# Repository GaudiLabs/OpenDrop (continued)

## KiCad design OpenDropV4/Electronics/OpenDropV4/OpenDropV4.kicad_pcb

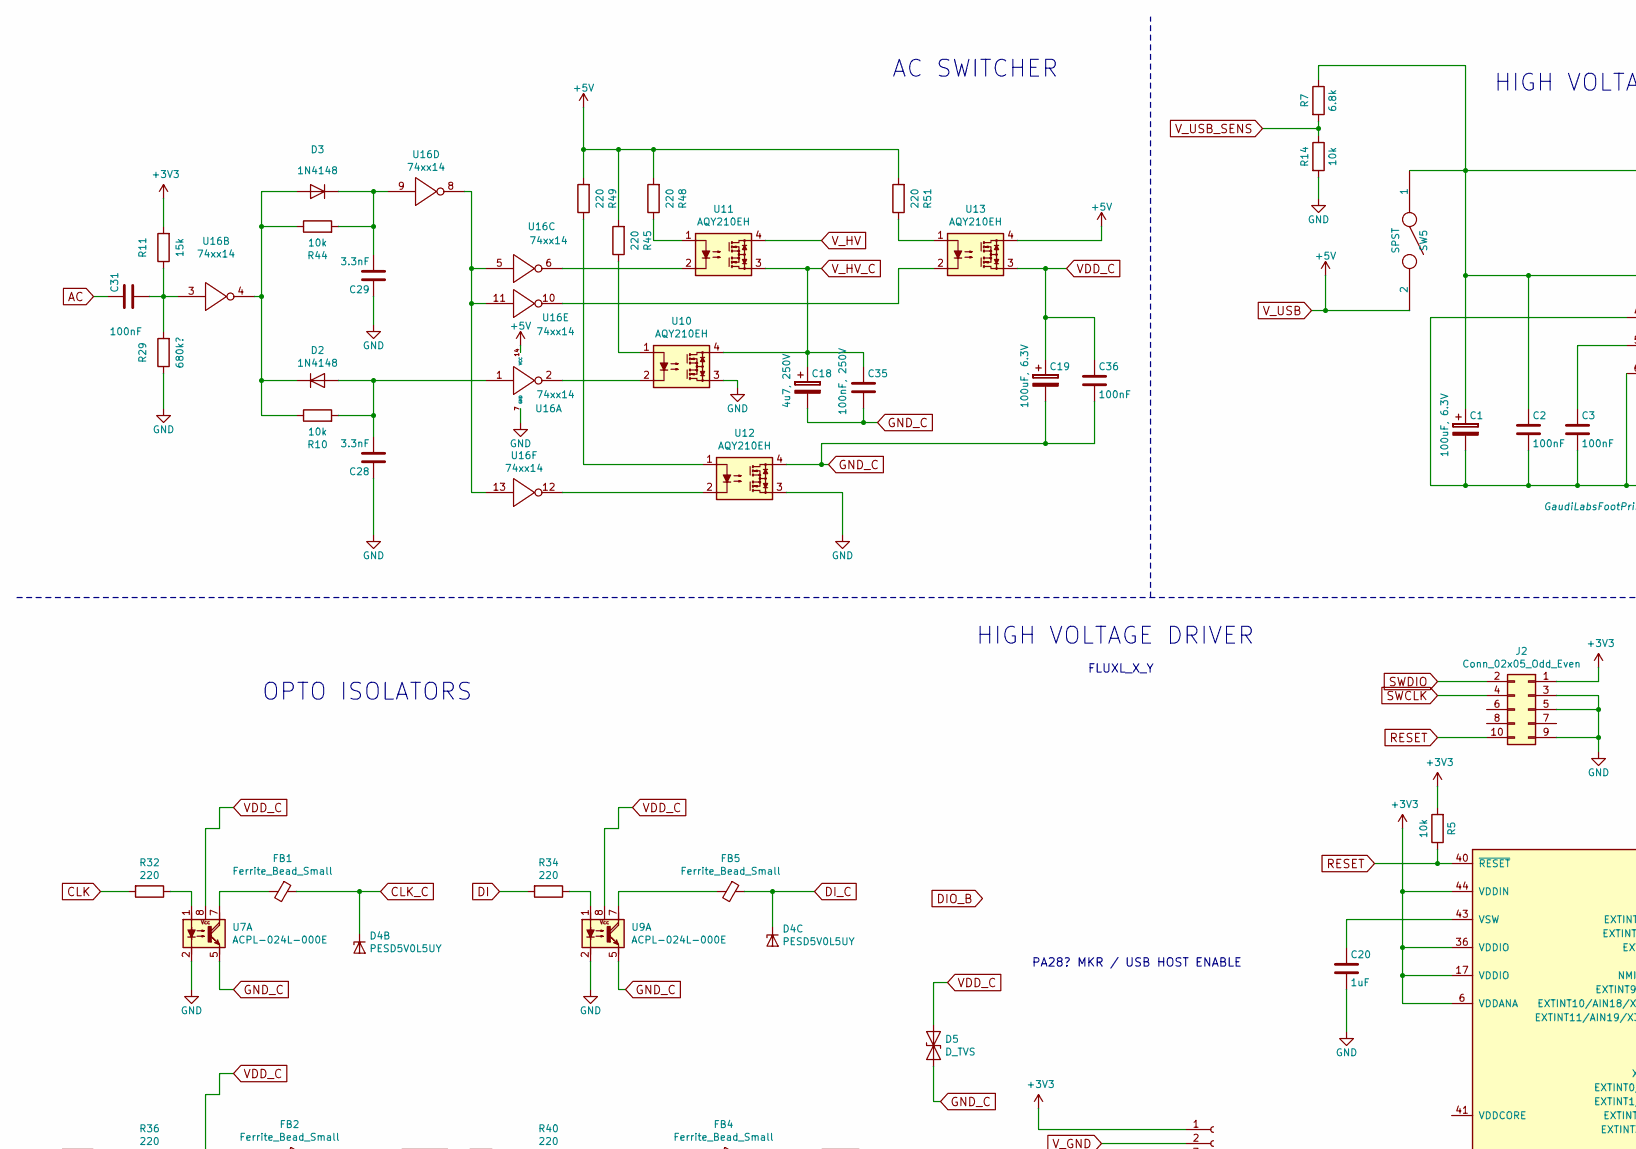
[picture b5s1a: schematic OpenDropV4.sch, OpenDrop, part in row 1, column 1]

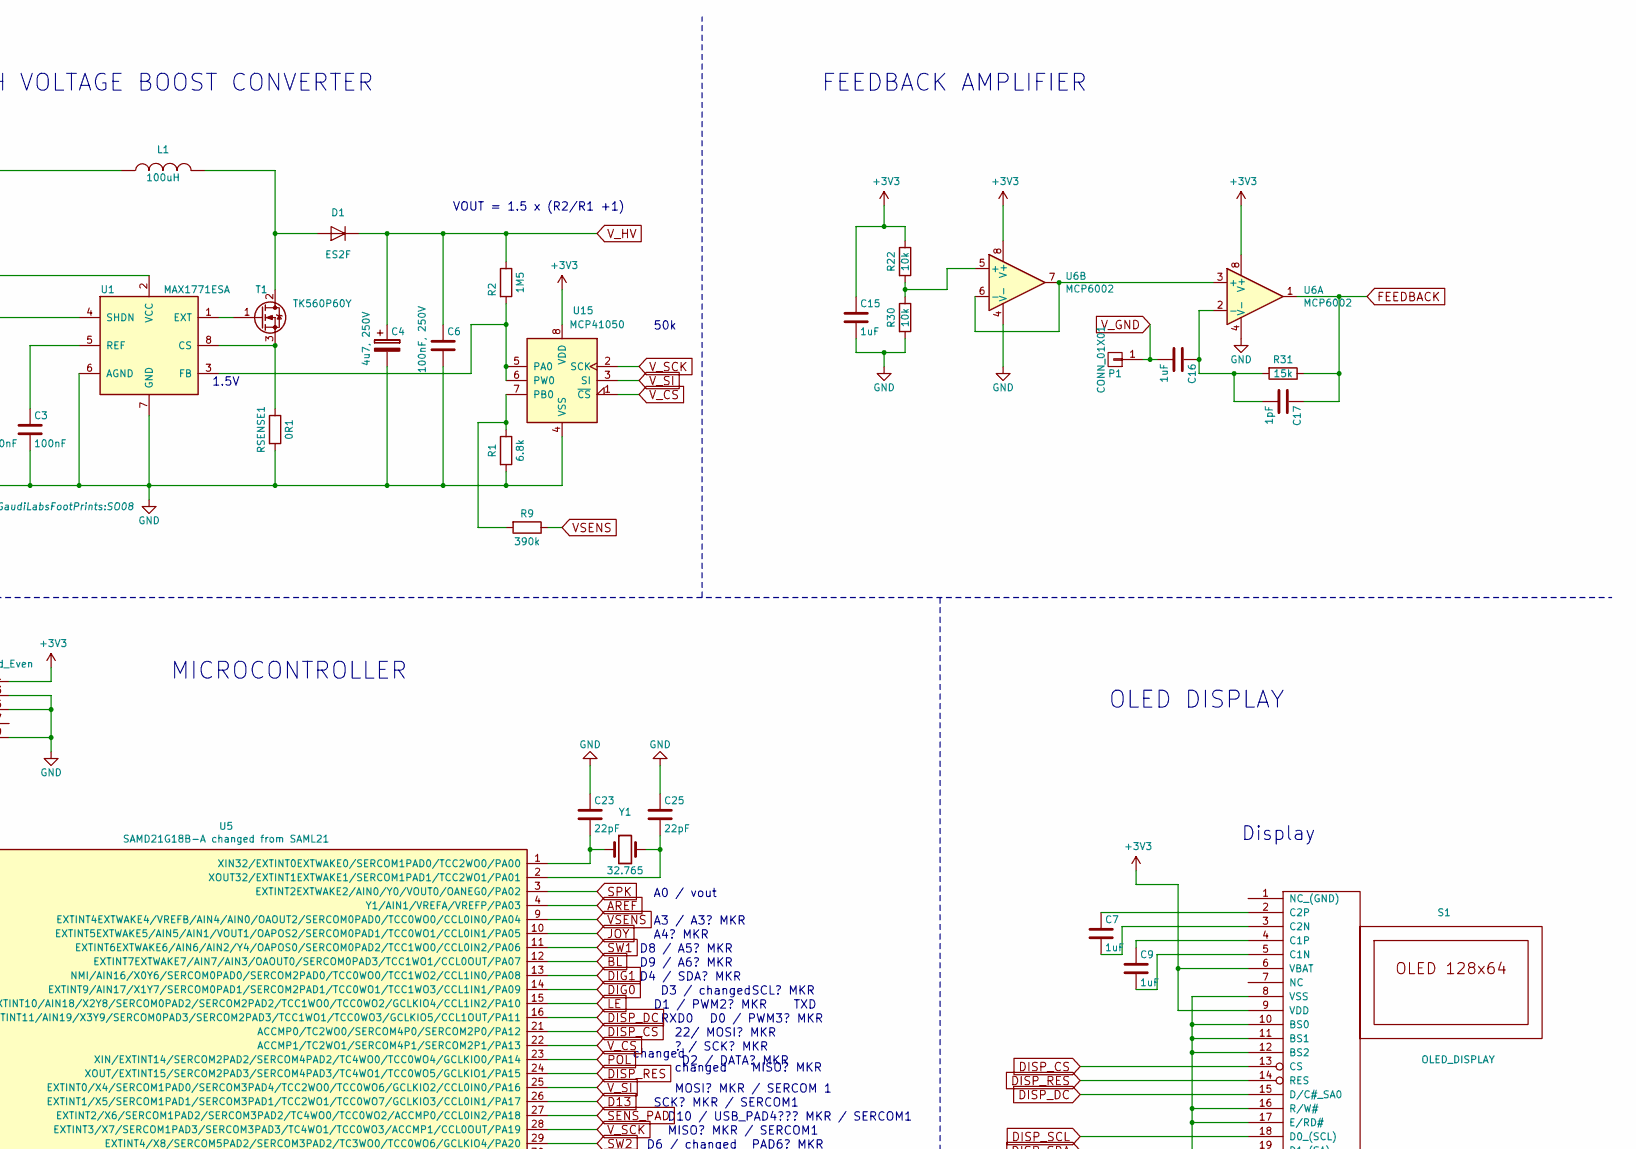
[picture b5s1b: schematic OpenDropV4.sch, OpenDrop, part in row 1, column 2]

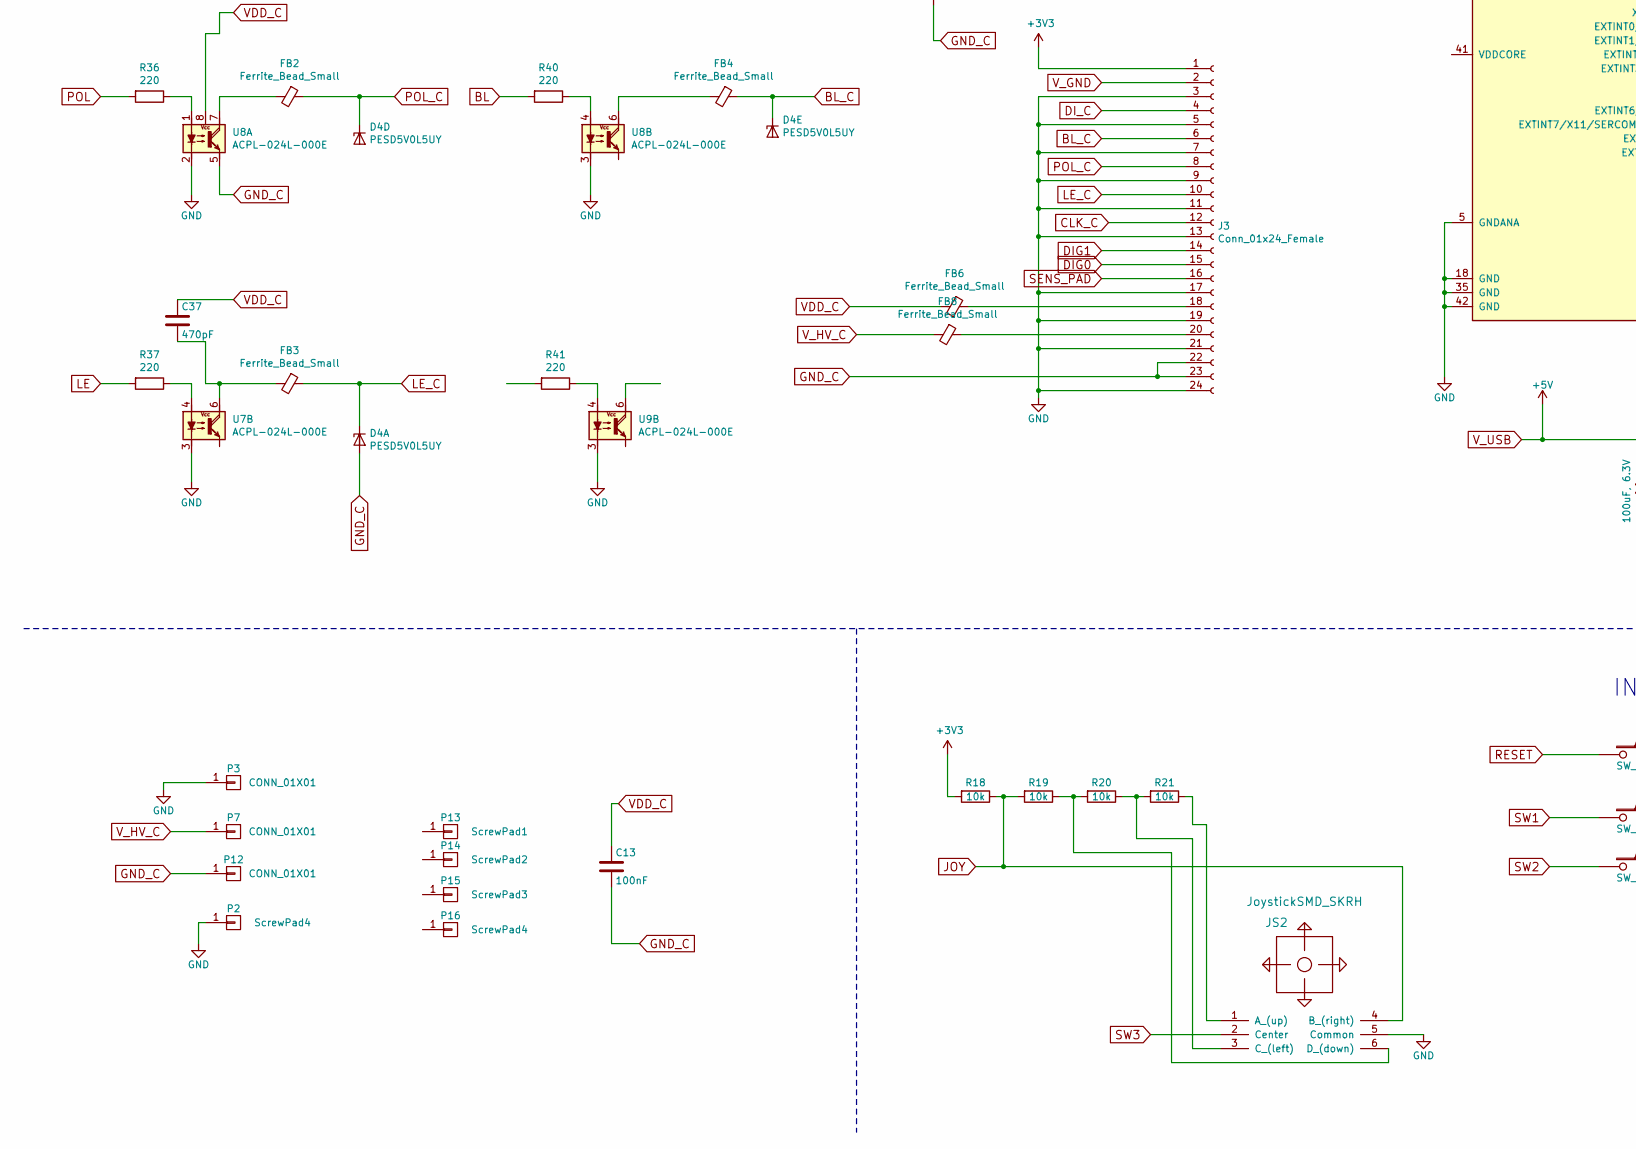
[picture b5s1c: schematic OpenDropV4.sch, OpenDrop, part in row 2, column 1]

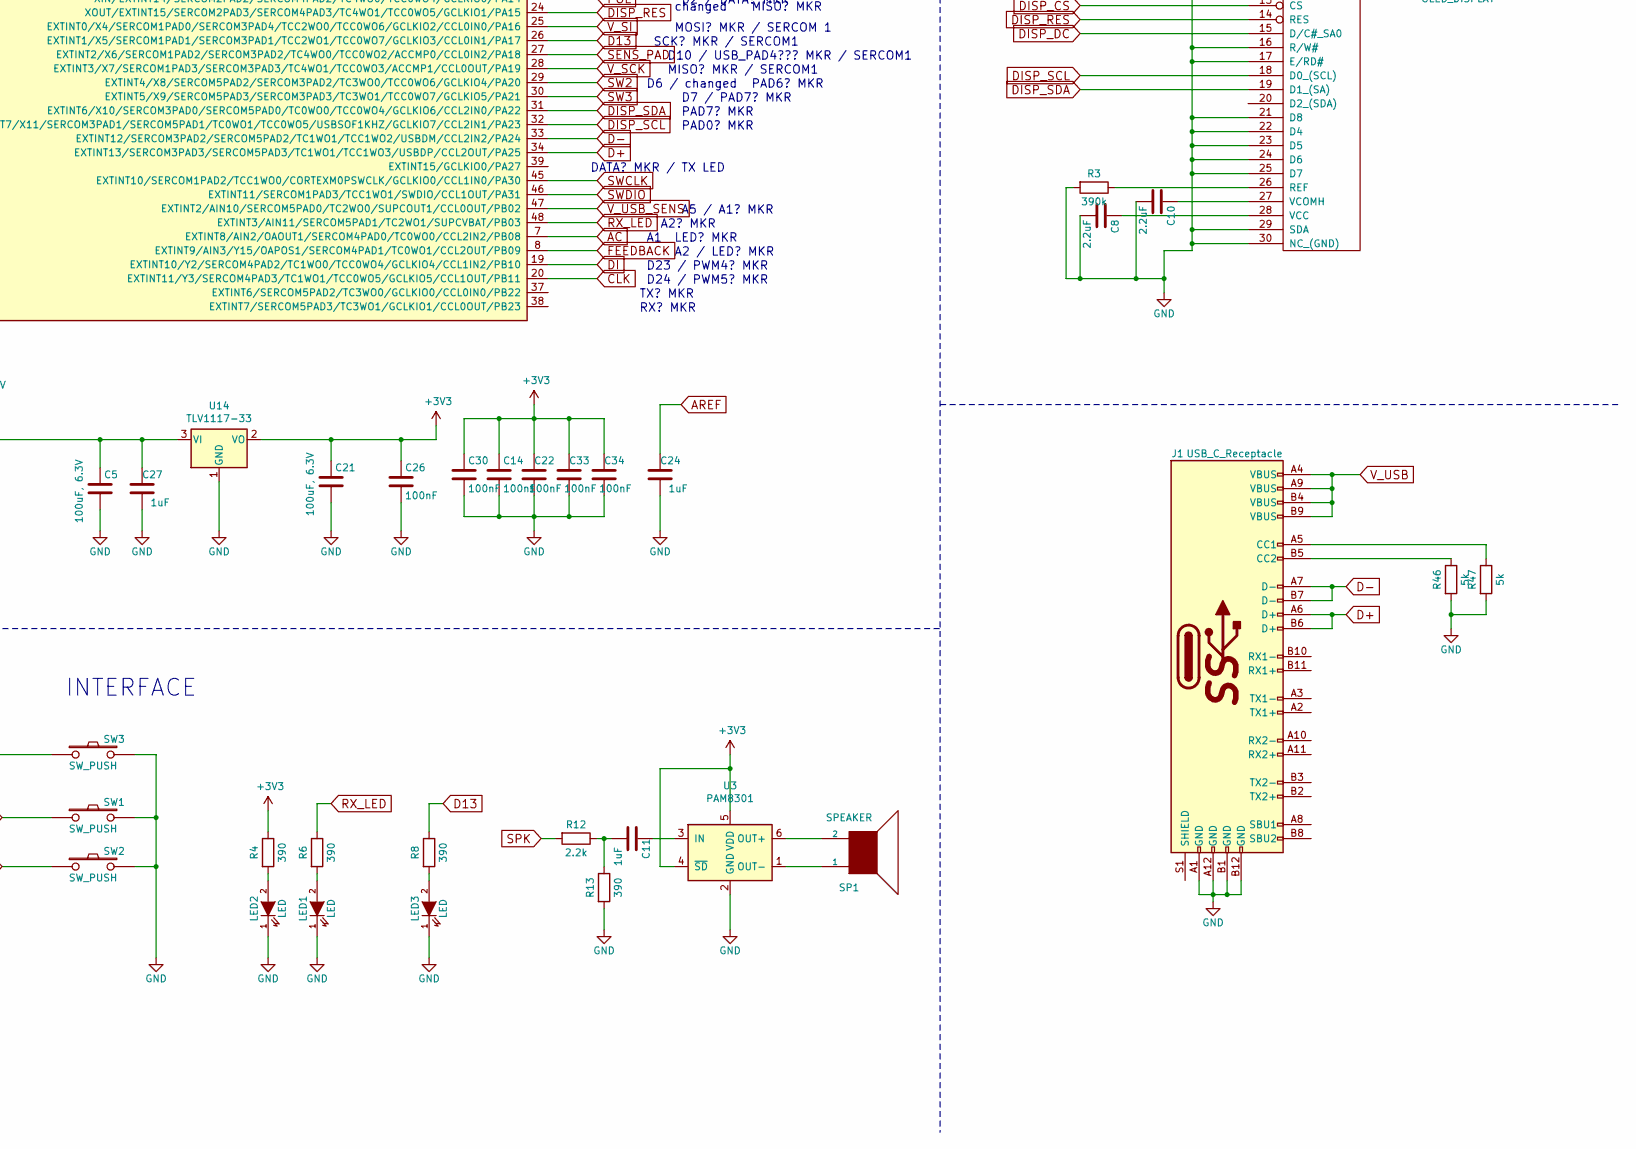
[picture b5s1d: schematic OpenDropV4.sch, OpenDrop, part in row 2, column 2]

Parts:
C1, C19: 100uF, 6.3V; C_1206_3216Metric
C2, C3, C13, C14, C22, C26, C30, C31, C33, C34, C36: 100nF; C_0805
C4, C18: 4u7, 250V; C_Elec_8x10.2
C5, C21: 100uF, 6.3V; C_1206
C6, C35: 100nF, 250V; C_1812_4532Metric_Pad1.30x3.40mm_HandSolder
C7, C9, C11, C15, C16, C20, C24, C27: 1uF; C_0805
C8, C10: 2.2uF; C_0805
C17: 1pF; C_0805
C23, C25: 22pF; C_0805
C28, C29: 3.3nF; C_0805
C37: 470pF; C_0805
D1: ES2F; DO-214AA
D2, D3: 1N4148; D_SOD-323
D4: PESD5V0L5UY; SOT-363_SC-70-6
D5: D_TVS; DO-214AA
FB1, FB2, FB3, FB4, FB5, FB6, FB8: Ferrite_Bead_Small; L_0603_1608Metric
J1: USB_C_Receptacle; USB_C_Receptacle_Amphenol_12401610E4-2A
J2: Conn_02x05_Odd_Even; Pin_Header_Straight_2x05_Pitch1.27mm_SMD
J3: Conn_01x24_Female; FFC_MOLEX_EASYON_05mm_24
JS2: JoystickSMD_SKRH; SKRHABE010
L1: 100uH; SRN1060
LED1, LED2, LED3: LED; LED_0603_1608Metric
P1, P3, P7, P12: CONN_01X01; Measurement_Point_Square-SMD-Pad_Small
P2: ScrewPad4; Measurement_Point_Croki
P13: ScrewPad1; MountingHoleM3
P14: ScrewPad2; MountingHoleM3
P15: ScrewPad3; MountingHoleM3
P16: ScrewPad4; MountingHoleM3
R1: 6.8k; R_0805
R2: 1M5; R_2512
R3, R9: 390k; R_0805
R4, R6, R8, R13: 390; R_0805
R5, R10, R18, R19, R20, R21, R22, R30, R44: 10k; R_0805
R7: 6.8k; R_0805_2012Metric
R11, R31: 15k; R_0805
R12: 2.2k; R_0805
R14: 10k; R_0805_2012Metric
R29: 680k?; R_0805
R32, R34, R36, R37, R40, R41, R45, R48, R49, R51: 220; R_0805
R46, R47: 5k; R_0805
RSENSE1: 0R1; R_2010
S1: OLED_DISPLAY; OLED_096_1_Flip
SP1: SPEAKER; Speaker16mm
SW1, SW2: SW_PUSH; PUSH_BUTTON_SMD
SW3: SW_PUSH; SW_SPST_KMS221GLFS
SW5: SPST; Switch_On-On
T1: TK560P60Y; D-Pak_TO252AA
U1: MAX1771ESA; SO08
U3: PAM8301; SOT-23-6
U5: SAMD21G18B-A changed from SAML21; TQFP-48_7x7mm_Pitch0.5mm
U6: MCP6002; SO08
U7, U8, U9: ACPL-024L-000E; HCPL_Optocoupler_SMD
U10, U11, U12, U13: AQY210EH; SMD_DIP4
U14: TLV1117-33; SOT-223
U15: MCP41050; SO08
U16: 74xx14; SOIC-14_N
Y1: 32.765; Crystal_SMD_3215-2pin_3.2x1.5mm

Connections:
+3V3: C14.1, C15.1, C21.1, C22.2, C26.1, C30.1, C33.2, C34.2, J2.1, J3.1, R4.1, R5.2, R11.2, R18.2, R22.1, S1.6 (VBAT), S1.9 (VDD), U3.4 (~SD), U3.5 (VDD), U5.6 (VDDANA), U5.17 (VDDIO), U5.36 (VDDIO), U5.44 (VDDIN), U6.8 (V+), U14.2 (VO), U15.8 (VDD)
AC: C31.1, U5.7 (EXTINT8/AIN2/OAOUT1/SERCOM4PAD0/TC0WO0/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)
AREF: C24.2, U5.4 (Y1/AIN1/VREFA/VREFP/PA03)
BL: R40.2, U5.12 (EXTINT7EXTWAKE7/AIN7/AIN3/OAOUT0/SERCOM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)
BL_C: D4.6 (K5), FB4.1, FB4.2, J3.6, U8.6 (COLLECTOR)
CLK: R32.2, U5.20 (EXTINT11/Y3/SERCOM4PAD3/TC1WO1/TCC0WO5/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)
CLK_C: D4.3 (K2), FB1.1, FB1.2, J3.12, U7.7 (COLLECTOR)
D13: R8.1, U5.26 (EXTINT1/X5/SERCOM1PAD1/SERCOM3PAD1/TCC2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)
D+: J1.A6 (D+), J1.B6 (D+), U5.34 (EXTINT13/SERCOM3PAD3/SERCOM5PAD3/TC1WO1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)
D-: J1.A7 (D-), J1.B7 (D-), U5.33 (EXTINT12/SERCOM3PAD2/SERCOM5PAD2/TC1WO1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)
DI: R34.2, U5.19 (EXTINT10/Y2/SERCOM4PAD2/TC1WO0/TCC0WO4/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)
DIG0: J3.15, U5.14 (EXTINT9/AIN17/X1Y7/SERCOM0PAD1/SERCOM2P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)
DISP_CS: S1.13 (CS), U5.21 (ACCMP0/TC2WO0/SERCOM4P0/SERCOM2P0/PA12)
DISP_DC: S1.15 (D/C#_SA0), U5.16 (EXTINT11/AIN19/X3Y9/SERCOM0PAD3/SERCOM2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)
DISP_RES: S1.14 (RES), U5.24 (XOUT/EXTINT15/SERCOM2PAD3/SERCOM4PAD3/T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)
DISP_SCL: S1.18 (D0_(SCL)), U5.32 (EXTINT7/X11/SERCOM3PAD1/SERCOM5PAD1/TC0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)
DISP_SDA: S1.19 (D1_(SA)), U5.31 (EXTINT6/X10/SERCOM3PAD0/SERCOM5PAD0/TC0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)
DI_C: D4.4 (K3), FB5.1, FB5.2, J3.4, U9.7 (COLLECTOR)
FEEDBACK: C17.1, R31.1, U5.8 (EXTINT9/AIN3/Y15/OAPOS1/SERCOM4PAD1/TC0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), U6.1
GND: C1.2, C2.2, C3.2, C4.2, C5.2, C6.2, C8.2, C10.2, C14.2, C15.2, C20.2, C21.2, C22.1, C23.1, C24.1, C25.1, C26.2, C27.1, C28.1, C29.1, C30.2, C33.1, C34.1, J1.A1 (GND), J1.A12 (GND), J1.B1 (GND), J1.B12 (GND), J2.3, J2.5, J2.9, J3.3, J3.5, J3.7, J3.9, J3.11, J3.13, J3.17, J3.19, J3.21, J3.24, JS2.5 (Common), LED1.1 (K), LED2.1 (K), LED3.1 (K), P2.1, P3.1, R1.2, R3.2, R13.2, R14.2, R29.1, R30.2, R46.2, R47.2, RSENSE1.2, S1.8 (VSS), S1.10 (BS0), S1.11 (BS1), S1.12 (BS2), S1.16 (R/W#), S1.17 (E/RD#), S1.21 (D8), S1.22 (D4), S1.23 (D5), S1.24 (D6), S1.25 (D7), S1.29 (SDA), S1.30 (NC_(GND)), SW1.2, SW2.2, SW3.2, U1.4 (SHDN), U1.6 (AGND), U1.7 (GND), U3.2 (GND), U5.5 (GNDANA), U5.18 (GND), U5.35 (GND), U5.42 (GND), U6.4 (V-), U7.2 (CATHODE), U7.3 (CATHODE), U8.2 (CATHODE), U8.3 (CATHODE), U9.2 (CATHODE), U9.3 (CATHODE), U10.3, U12.3, U14.1 (GND), U15.4 (VSS), U16.7 (GND)
GND_C: C13.2, C18.2, C19.2, C35.2, C36.2, D4.2 (A), D5.2 (A2), J3.22, J3.23, P12.1, U7.5, U8.5, U9.5, U12.4
JOY: JS2.4 (B_(right)), R18.1, R19.2, U5.10 (EXTINT5EXTWAKE5/AIN5/AIN1/VOUT1/OAPOS2/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)
unnamed: C1.1, C2.1, L1.1, R7.1, SW5.1, U1.2 (VCC)
unnamed: C3.1, U1.5 (REF)
unnamed: C7.1, S1.2 (C2P)
unnamed: C7.2, S1.3 (C2N)
unnamed: C8.1, S1.28 (VCC)
unnamed: C9.1, S1.4 (C1P)
unnamed: C9.2, S1.5 (C1N)
unnamed: C10.1, S1.27 (VCOMH)
unnamed: C11.1, R12.1, R13.1
unnamed: C11.2, U3.3 (IN)
unnamed: C16.1, C17.2, R31.2, U6.2 (-)
unnamed: C20.1, U5.43 (VSW)
unnamed: C23.2, U5.1 (XIN32/EXTINT0EXTWAKE0/SERCOM1PAD0/TCC2W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), Y1.1
unnamed: C25.2, U5.2 (XOUT32/EXTINT1EXTWAKE1/SERCOM1PAD1/TCC2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), Y1.2
unnamed: C28.2, D2.2 (A), R10.2, U16.1
unnamed: C29.2, D3.1 (K), R44.2, U16.9
unnamed: C31.2, R11.1, R29.2, U16.3
unnamed: D1.2 (A), L1.2, T1.2 (D)
unnamed: D2.1 (K), D3.2 (A), R10.1, R44.1, U16.4
unnamed: J1.A5 (CC1), R47.1
unnamed: J1.B5 (CC2), R46.1
unnamed: JS2.1 (A_(up)), R21.1
unnamed: JS2.3 (C_(left)), R20.1, R21.2
unnamed: JS2.6 (D_(down)), R19.1, R20.2
unnamed: LED1.2 (A), R6.2
unnamed: LED2.2 (A), R4.2
unnamed: LED3.2 (A), R8.2
unnamed: R1.1, R9.2, U15.7 (PB0)
unnamed: R2.2, U1.3 (FB), U15.5 (PA0), U15.6 (PW0)
unnamed: R3.1, S1.26 (REF)
unnamed: R7.2, R14.1, U5.47 (EXTINT2/AIN10/SERCOM5PAD0/TC2WO0/SUPCOU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)
unnamed: R22.2, R30.1, U6.5 (+)
unnamed: R32.1, U7.1 (ANODE)
unnamed: R34.1, U9.1 (ANODE)
unnamed: R36.1, U8.1 (ANODE)
unnamed: R37.1, U7.4 (ANODE)
unnamed: R40.1, U8.4 (ANODE)
unnamed: R41.1, U9.4 (ANODE)
unnamed: R45.1, U10.1
unnamed: R48.1, U11.1
unnamed: R49.1, U12.1
unnamed: R51.1, U13.1
unnamed: RSENSE1.1, T1.3 (S), U1.8 (CS)
unnamed: SP1.1, U3.1 (OUT-)
unnamed: SP1.2, U3.6 (OUT+)
unnamed: T1.1 (G), U1.1 (EXT)
unnamed: U6.3 (+), U6.6 (-), U6.7
unnamed: U10.2, U16.2
unnamed: U11.2, U16.6
unnamed: U12.2, U16.12
unnamed: U13.2, U16.10
unnamed: U16.5, U16.8, U16.11, U16.13
POL: R36.2, U5.23 (XIN/EXTINT14/SERCOM2PAD2/SERCOM4PAD2/TC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)
POL_C: D4.5 (K4), FB2.1, FB2.2, J3.8, U8.7 (COLLECTOR)
RESET: J2.10, R5.1, SW3.1, U5.40 (~RESET~)
RX_LED: R6.1, U5.48 (EXTINT3/AIN11/SERCOM5PAD1/TC2WO1/SUPCVB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)
SENS_PAD: J3.16, U5.27 (EXTINT2/X6/SERCOM1PAD2/SERCOM3PAD2/TC4W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)
SPK: R12.2, U5.3 (EXTINT2EXTWAKE2/AIN0/Y0/VOUT0/OANEG0/PA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)
SW1: SW1.1, U5.11 (EXTINT6EXTWAKE6/AIN6/AIN2/Y4/OAPOS0/SER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)
SW2: SW2.1, U5.29 (EXTINT4/X8/SERCOM5PAD2/SERCOM3PAD2/TC3W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)
SW3: JS2.2 (Center), U5.30 (EXTINT5/X9/SERCOM5PAD3/SERCOM3PAD3/TC3W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)
SWCLK: J2.4, U5.45 (EXTINT10/SERCOM1PAD2/TCC1WO0/CORTEXM0PS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)
SWDIO: J2.2, U5.46 (EXTINT11/SERCOM1PAD3/TCC1WO1/SWDIO/CCL1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)
VDD_C: C13.1, C19.1, C36.1, C37.1, D5.1 (A1), FB6.1, FB6.2, J3.18, U7.8 (VCC), U8.8 (VCC), U9.8 (VCC), U13.3
VSENS: R9.1, U5.9 (EXTINT4EXTWAKE4/VREFB/AIN4/AIN0/OAOUT2/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)
V_CS: U5.22 (ACCMP1/TC2WO1/SERCOM4P1/SERCOM2P1/PA13), U15.1 (~CS)
V_GND: C16.2, J3.2, P1.1
V_HV: C4.1, C6.1, D1.1 (K), R2.1, U11.4
V_HV_C: C18.1, C35.1, FB8.1, FB8.2, J3.20, P7.1, U10.4, U11.3
V_SCK: U5.28 (EXTINT3/X7/SERCOM1PAD3/SERCOM3PAD3/TC4W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), U15.2 (SCK)
V_SI: U5.25 (EXTINT0/X4/SERCOM1PAD0/SERCOM3PAD4/TCC2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), U15.3 (SI)
V_USB: C5.1, C27.2, J1.A4 (VBUS), J1.A9 (VBUS), J1.B4 (VBUS), J1.B9 (VBUS), R45.2, R48.2, R49.2, R51.2, SW5.2, U13.4, U14.3 (VI), U16.14 (VCC)

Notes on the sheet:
VOUT = 1.5 x (R2/R1 +1)
Display
AC SWITCHER
HIGH VOLTAGE BOOST CONVERTER
FEEDBACK AMPLIFIER
INTERFACE
HIGH VOLTAGE DRIVER
OPTO ISOLATORS
MICROCONTROLLER
OLED DISPLAY
D6 / changed
A0 / vout
changed
50k
D3 / changed
LED? MKR
A3 / A3? MKR
A4? MKR
D8 / A5? MKR
D9 / A6? MKR
D4 / SDA? MKR
SCL? MKR
D1 / PWM2? MKR
D0 / PWM3? MKR
D23 / PWM4? MKR
D24 / PWM5? MKR
22/ MOSI? MKR
? / SCK? MKR
D2 / DATA? MKR
MISO? MKR
MOSI? MKR / SERCOM 1
SCK? MKR / SERCOM1
D10 / USB_PAD4??? MKR / SERCOM1
MISO? MKR / SERCOM1
PAD6? MKR
D7 / PAD7? MKR
PAD7? MKR
PAD0? MKR
TX? MKR
RX? MKR

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
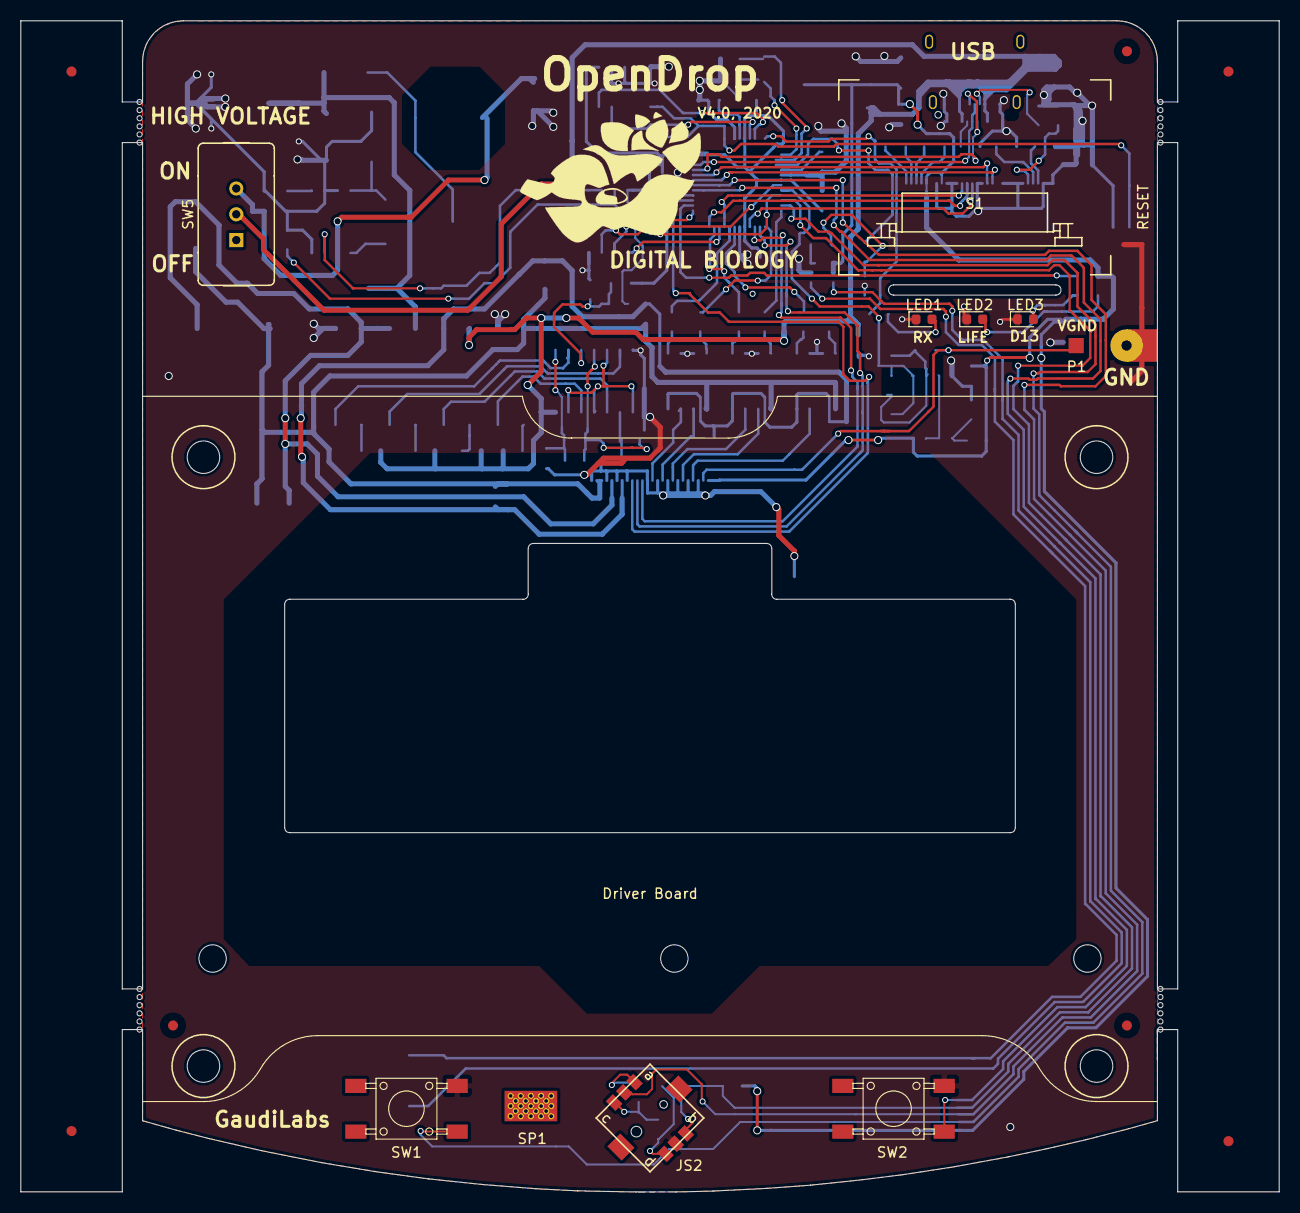
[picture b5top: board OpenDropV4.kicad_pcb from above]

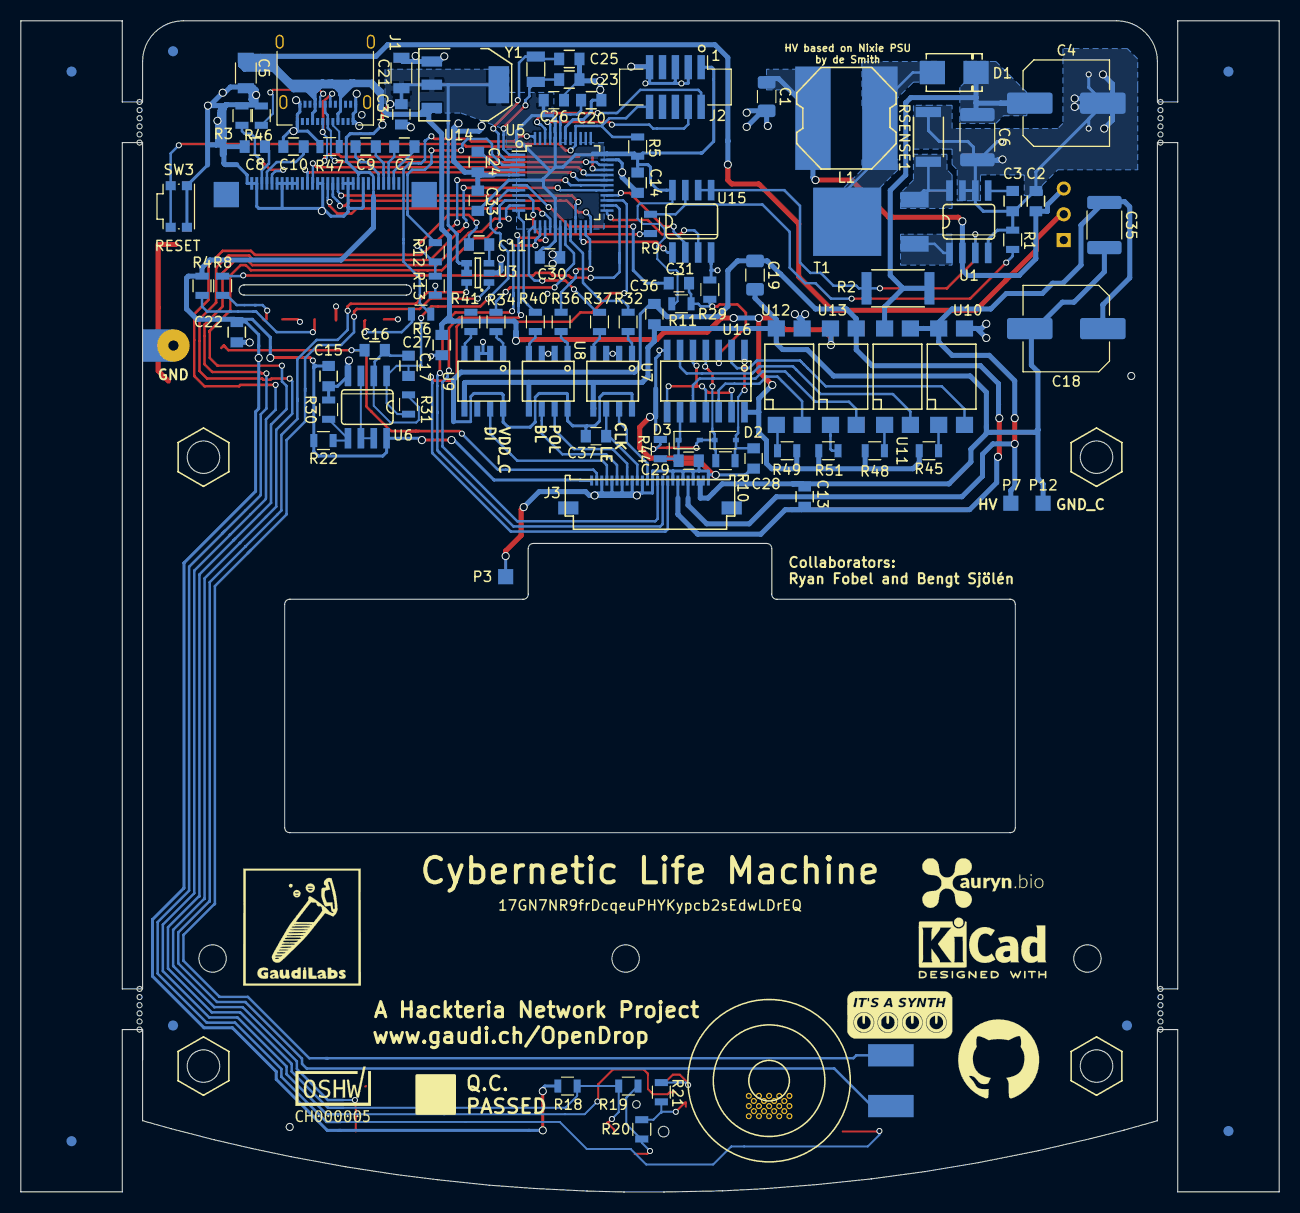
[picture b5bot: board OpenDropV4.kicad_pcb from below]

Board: 2 copper layers, 124.0 x 115.4 mm, 111 parts (96 on the bottom side), 96 nets.

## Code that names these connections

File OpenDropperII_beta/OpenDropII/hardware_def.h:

#define FluxlPad_width 16
#define FluxlPad_heigth 8


// If using software SPI (the default case):
#define OLED_MOSI   2
#define OLED_CLK   3
#define OLED_DC    11
#define OLED_CS    12
#define OLED_RESET 13



#define BL_pin         9           // BL Pin
#define LE_pin          4           // LE Pin
#define CLK_pin         15           // CLK Pin
#define DI_pin         16           // Digital Out Pin
#define POL_pin         A1           // Digital Out Pin


#define SW1_pin         8           // Left button
#define SW2_pin         A5           // Right button
#define SW3_pin         7           // Joy button
#define JOY_pin         A4           // JOY_pin analog 
#define FEEDBACK_pin    A2           // FEEDBACK pin



#define ESP_RESET_pin   A3           // Buton 1 pin
#define ESP_GPIO0_pin   10           // Buton 1 pin
#define ESP_RX_pin      1           // Buton 1 pin
#define ESP_TX_pin      0           // Buton 1 pin

#define LED_LIGHT_pin         5           // Digital  Pin for LEDs
#define SPK_pin       6           // Digital Pin for speaker

#define sound_flag true           // Make Sound
#define light_flag false           // Make Light

#define feedback_flag false           // Make Light

const byte FluxelID [16][8] PROGMEM ={
{3,2,1,0,63,62,61,60},
{6,7,5,4,59,58,56,57},
{10,9,11,8,55,52,54,53},
{13,14,15,12,51,48,49,50},
{17,18,19,16,47,44,45,46},
{20,21,22,23,40,41,42,43},
{24,28,27,31,32,37,35,39},
{29,25,26,30,33,36,38,34},
{98,102,100,97,94,90,89,93},
{103,99,101,96,95,91,92,88},
{107,106,105,104,87,86,85,84},
{110,109,108,111,80,83,82,81},
{114,113,112,115,76,79,78,77},
{117,118,116,119,72,75,73,74},
{121,120,122,123,68,69,71,70},
{124,125,126,127,64,65,66,67}};



 const byte pad_lookup_x [64] PROGMEM = {
0,0,0,0,1,1,1,1,
2,2,2,2,3,3,3,3,
4,4,4,4,5,5,5,5,
6,7,7,6,6,7,7,6,
6,7,7,6,7,6,7,6,
5,5,5,5,4,4,4,4,
3,3,3,3,2,2,2,2,
1,1,1,1,0,0,0,0
};

const byte pad_lookup_y [64] PROGMEM = {
3,2,1,0,3,2,0,1,
3,1,0,2,3,0,1,2,
3,0,1,2,0,1,2,3,
0,1,2,2,1,0,3,3,
4,4,7,6,5,5,6,7,
4,5,6,7,5,6,7,4,
5,6,7,4,5,7,6,4,
6,7,5,4,7,6,5,4
};

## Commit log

2014-10-29 Version 2.1
2016-02-15 updated Repositoty
    more soon...
2016-02-15 OpenDrop V2
    Complete design files of OpenDrop V2 Proto
2016-02-15 Updated README and added license file
    just to make sure.
2016-02-15 Updated README for V2
2016-03-07 changed library paths to be relative and point to GaudiLabsPartsLibrary and arduino_micro_shield within the repository
2016-04-28 started with corrections for V2.1
    work in progress
2016-05-03 More modifications and corrections for Version 2.1
    work in progress
2016-05-09 added interfacing for esp-01 module, moved sda/scl, removed p3, moved BL
2016-05-09 changed pin numbering on esp-01 module symbol
2016-05-09 untracked backup and cache files
2016-05-09 esp8266 symbols and footprints
2016-05-09 not tracking runtime files
2016-05-09 first try at making open drop with esp201 only and no micro
2016-05-09 put fet at ground for led lights
2016-05-11 Production Version of V2.1
    Hopefully...
2016-05-12 Production Version 2.1 with Gerber Files
    Version Bittie
2016-05-20 Added paste masks as SVG
2016-05-24 cleaned up folder structure
    V2-ESP01 and C2-ESP201
2016-05-24 Cerrected library path settings
2016-05-25 Added OpenDropper Code
    Thanks Bengt for the new name.
2016-05-25 New Readme
2016-06-02 Added Carrier and BOM21
2016-09-26 Updated Arduino Code to V2.1
2016-09-26 Added display library
2016-10-13 Updated to Version 2.1
2016-10-13 Changed Folder Name to V2.1
2017-04-07 Added new OpenDrop Library beta version
2017-09-19 added pdf of schematic
2017-12-06 First release OpenDrop V3 yuhuu
2018-04-10 Improved design and corrected some errors. Allmost there
2018-04-24 Updated OpenDrop V3 to V3.1 and waiting for the PCBs
2018-06-12 Added OpenDropper V3 Arduino (Adafruit Feather M0) code to run OpenDrop V3
2018-06-15 Added OpenDrop App First commit
2018-07-10 Add USB C pulldowns
    Fixes #12
2018-07-11 Connect speaker driver to 3.3V (instead of 5V)
2018-07-11 Add MPN field to parts in schematic
2018-07-26 Version 3.2 allmost done
2018-08-03 Update V3.1 for mechanical parts
2018-08-06 Updated to V3_2 Rearranged Folder
2018-08-06 Removed old Gerber Folder Not sure this is the way to do it...
2018-08-07 Updated to V32 new marked with (new)
2018-09-14 Production Files V3_2 This is it.
2018-10-22 Updated the embedded and the PC software see also documentation online
2019-06-07 Updated Version of the OpenDrop Controller App Window can scale now.
2019-07-23 Named Version That's it.
2020-04-07 Added Version 4 Modular OpenDrop
2020-04-29 Ready for second prototype round its not a synth
2020-07-01 Production Version OpenDrop V4 All PCBs, BOMs, Materials and Software
2020-11-27 New version of OpenDrop Controller
2021-03-31 First design of Magnet Adapter Let's test it.
2021-05-14 added STEP 3D files for your VR
2021-08-02 Updated to V4.1 in Software and Electronics
2021-08-02 Updated Controller V4_2 because..
2021-08-02 Updated V3_2 because
2021-11-04 Changed "showMessageDialog" pointer to null to be compatible with V4 hopefully
2021-12-02 Initializing ADC settings for AnalogRead and cleaned up some files.
2021-12-03 Downgrading display library cause a glitch will have to find cause at some point
2022-06-03 Added Feedback Reading and many updates to hard and software
2022-06-17 Corrected filename to match with folder Removed the strange P2D
2023-11-20 Update and new catridge with heated pads
2024-10-18 added new json
2024-10-21 Updated Module Adapter Basic with protection resistors
2024-10-21 Adapter Basic
2025-07-01 correction in OpenDrop::begin just that
2025-07-03 Edited README.md to improve description of project
